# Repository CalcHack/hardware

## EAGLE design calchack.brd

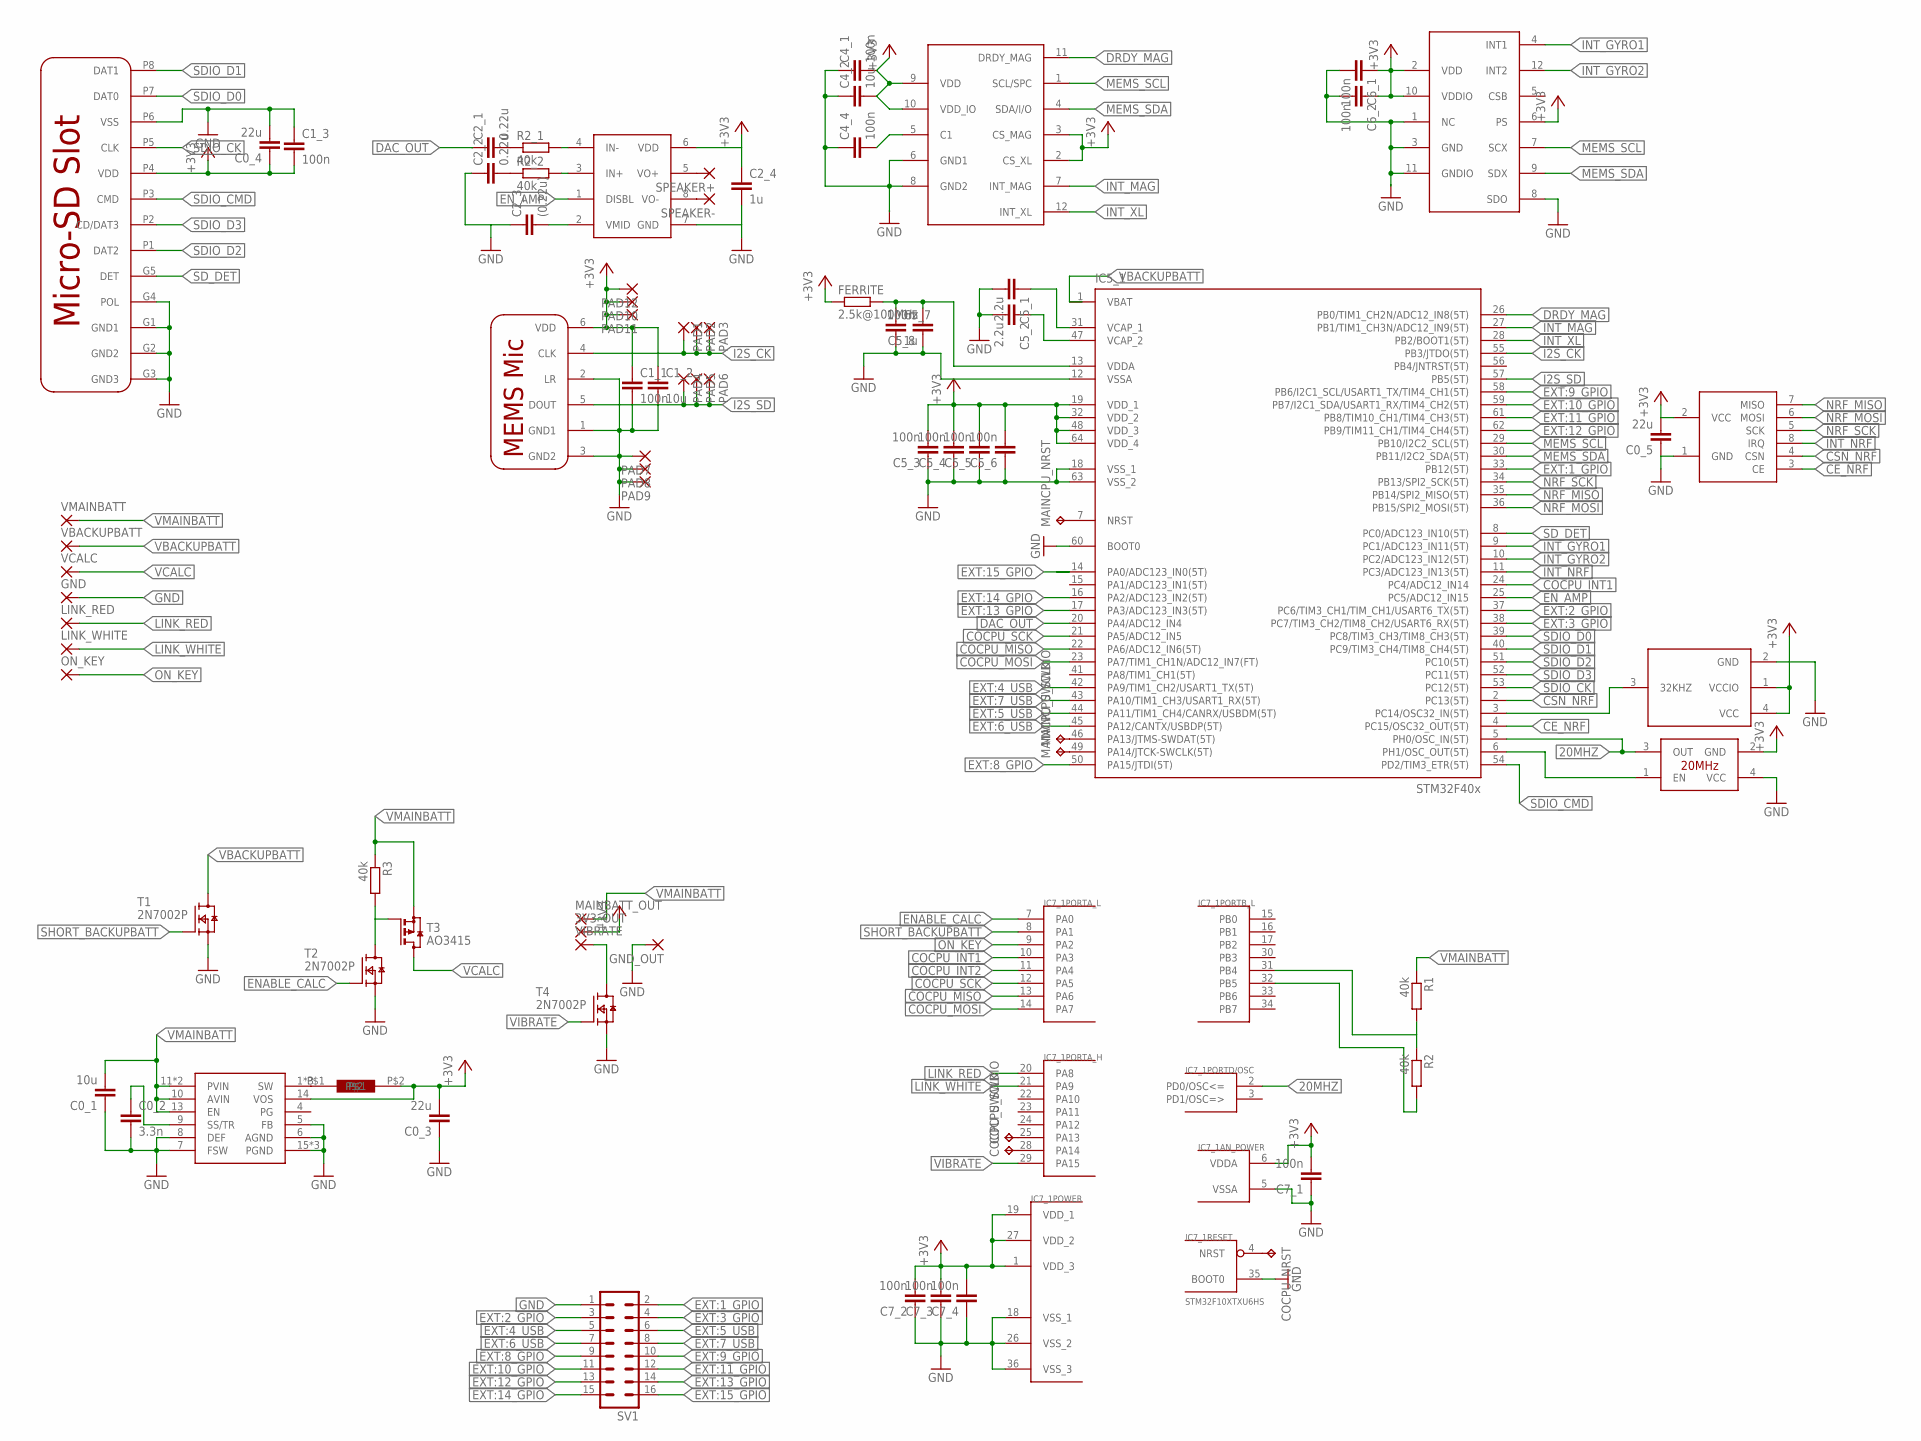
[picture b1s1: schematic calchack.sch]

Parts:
3V3_OUT: 1,6/0,8
C0_1: 10u; C0805
C0_2: 3.3n; C0603
C0_3, C0_4, C0_5: 22u; C0805
C1_1, C1_3, C4_1, C4_4, C5_3, C5_4, C5_5, C5_6, C5_8, C6_1, C6_2, C7_1, C7_2, C7_3, C7_4: 100n; C0603
C1_2, C4_2: 10u; C0603
C2_1, C2_2: 0.22u; C0603
C2_3: (0.22u); C0603
C2_4, C5_7: 1u; C0603
C5_1, C5_2: 2.2u; C0603
COCPU_NRST: TPTP10SQ; TP10SQ
COCPU_SWCLK: TPTP10SQ; TP10SQ
COCPU_SWDIO: TPTP10SQ; TP10SQ
FERRITE: 2.5k@100MHz; R0603
GND: 1,6/0,8
GND_OUT: 1,6/0,8
IC0_1: TPS62142
IC1_1: MP45DT02
IC2_1: TPA6211A1
IC3_1: 475710001
IC4_1: LSM303C
IC5_1: STM32F405R; TQFP64
IC6_1: BMG160
IC7_1: STM32F10XTXU6HS; VFQFPN36-HS
L0_1: IHLP1212BZER2R2M11
LINK_RED: 1,6/0,8
LINK_WHITE: 1,6/0,8
MAINBATT_OUT: 1,6/0,8
MAINCPU_NRST: TPTP10SQ; TP10SQ
MAINCPU_SWCLK: TPTP10SQ; TP10SQ
MAINCPU_SWDIO: TPTP10SQ; TP10SQ
NRF24L01: NRF24L01
ON_KEY: 1,6/0,8
OSC5_1: SG-3030JC
PAD1, PAD2, PAD3, PAD4, PAD5, PAD6, PAD7, PAD8, PAD9, PAD10, PAD11, PAD12: 1,6/0,8
R1, R2, R2_1, R2_2, R3: 40k; R0603
SPEAKER+: 1,6/0,8
SPEAKER-: 1,6/0,8
SV1: MA08-2
T1, T2, T4: 2N7002P; SOT23
T3: AO3415
U$1: ASDMB-20.000MHZ-LC-T
VBACKUPBATT: 1,6/0,8
VCALC: 1,6/0,8
VIBRATE: 1,6/0,8
VMAINBATT: 1,6/0,8

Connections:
20MHZ: IC5_1.5 (PH0/OSC_IN(5T)), IC7_1.2 (PD0/OSC<=), U$1.3 (OUT)
+3V3: 3V3_OUT.1, C0_3.2, C0_4.1, C0_5.2, C1_1.1, C1_2.1, C1_3.2, C2_4.1, C4_1.2, C4_2.2, C5_3.2, C5_4.2, C5_5.2, C5_6.2, C6_1.1, C6_2.1, C7_1.2, C7_2.2, C7_3.2, C7_4.2, FERRITE.1, IC0_1.14 (VOS), IC1_1.6 (VDD), IC2_1.6 (VDD), IC3_1.P4 (VDD), IC4_1.2 (CS_XL), IC4_1.3 (CS_MAG), IC4_1.9 (VDD), IC4_1.10 (VDD_IO), IC5_1.19 (VDD_1), IC5_1.32 (VDD_2), IC5_1.48 (VDD_3), IC5_1.64 (VDD_4), IC6_1.2 (VDD), IC6_1.6 (PS), IC6_1.10 (VDDIO), IC7_1.1 (VDD_3), IC7_1.6 (VDDA), IC7_1.19 (VDD_1), IC7_1.27 (VDD_2), L0_1.P$2, NRF24L01.2 (VCC), OSC5_1.1 (VCCIO), OSC5_1.4 (VCC), PAD10.1, PAD11.1, PAD12.1, U$1.2 (GND)
CE_NRF: IC5_1.4 (PC15/OSC32_OUT(5T)), NRF24L01.3 (CE)
COCPU_INT1: IC5_1.24 (PC4/ADC12_IN14), IC7_1.10 (PA3)
COCPU_INT2: IC7_1.11 (PA4)
COCPU_MISO: IC5_1.22 (PA6/ADC12_IN6(5T)), IC7_1.13 (PA6)
COCPU_MOSI: IC5_1.23 (PA7/TIM1_CH1N/ADC12_IN7(FT)), IC7_1.14 (PA7)
COCPU_SCK: IC5_1.21 (PA5/ADC12_IN5), IC7_1.12 (PA5)
CSN_NRF: IC5_1.2 (PC13(5T)), NRF24L01.4 (CSN)
DAC_OUT: C2_1.1, IC5_1.20 (PA4/ADC12_IN4)
DRDY_MAG: IC4_1.11 (DRDY_MAG), IC5_1.26 (PB0/TIM1_CH2N/ADC12_IN8(5T))
ENABLE_CALC: IC7_1.7 (PA0), T2.1 (G)
EN_AMP: IC2_1.1 (DISBL), IC5_1.25 (PC5/ADC12_IN15)
EXT:1_GPIO: IC5_1.33 (PB12(5T)), SV1.2
EXT:2_GPIO: IC5_1.37 (PC6/TIM3_CH1/TIM_CH1/USART6_TX(5T)), SV1.3
EXT:3_GPIO: IC5_1.38 (PC7/TIM3_CH2/TIM8_CH2/USART6_RX(5T)), SV1.4
EXT:4_USB: IC5_1.42 (PA9/TIM1_CH2/USART1_TX(5T)), SV1.5
EXT:5_USB: IC5_1.44 (PA11/TIM1_CH4/CANRX/USBDM(5T)), SV1.6
EXT:6_USB: IC5_1.45 (PA12/CANTX/USBDP(5T)), SV1.7
EXT:7_USB: IC5_1.43 (PA10/TIM1_CH3/USART1_RX(5T)), SV1.8
EXT:8_GPIO: IC5_1.50 (PA15/JTDI(5T)), SV1.9
EXT:9_GPIO: IC5_1.58 (PB6/I2C1_SCL/USART1_TX/TIM4_CH1(5T)), SV1.10
EXT:10_GPIO: IC5_1.59 (PB7/I2C1_SDA/USART1_RX/TIM4_CH2(5T)), SV1.11
EXT:11_GPIO: IC5_1.61 (PB8/TIM10_CH1/TIM4_CH3(5T)), SV1.12
EXT:12_GPIO: IC5_1.62 (PB9/TIM11_CH1/TIM4_CH4(5T)), SV1.13
EXT:13_GPIO: IC5_1.17 (PA3/ADC123_IN3(5T)), SV1.14
EXT:14_GPIO: IC5_1.16 (PA2/ADC123_IN2(5T)), SV1.15
EXT:15_GPIO: IC5_1.14 (PA0/ADC123_IN0(5T)), SV1.16
GND: C0_1.1, C0_2.2, C0_3.1, C0_4.2, C0_5.1, C1_1.2, C1_2.2, C1_3.1, C2_2.1, C2_3.1, C2_4.2, C4_1.1, C4_2.1, C4_4.1, C5_1.2, C5_2.2, C5_3.1, C5_4.1, C5_5.1, C5_6.1, C5_7.2, C5_8.1, C6_1.2, C6_2.2, C7_1.1, C7_2.1, C7_3.1, C7_4.1, GND.1, GND_OUT.1, IC0_1.5 (FB), IC0_1.6 (AGND), IC0_1.7 (FSW), IC0_1.8 (DEF), IC0_1.15 (PGND), IC0_1.16 (PGND), IC0_1.TH (PGND), IC1_1.1 (GND1), IC1_1.2 (LR), IC1_1.3 (GND2), IC2_1.7 (GND), IC3_1.G1 (GND1), IC3_1.G2 (GND2), IC3_1.G3 (GND3), IC3_1.G4 (POL), IC3_1.P6 (VSS), IC4_1.6 (GND1), IC4_1.8 (GND2), IC5_1.12 (VSSA), IC5_1.18 (VSS_1), IC5_1.60 (BOOT0), IC5_1.63 (VSS_2), IC6_1.1 (NC), IC6_1.3 (GND), IC6_1.8 (SDO), IC6_1.11 (GNDIO), IC7_1.5 (VSSA), IC7_1.18 (VSS_1), IC7_1.26 (VSS_2), IC7_1.35 (BOOT0), IC7_1.36 (VSS_3), NRF24L01.1 (GND), OSC5_1.2 (GND), PAD7.1, PAD8.1, PAD9.1, SV1.1, T1.2 (S), T2.2 (S), T4.2 (S), U$1.4 (VCC)
I2S_CK: IC1_1.4 (CLK), IC5_1.55 (PB3/JTDO(5T)), PAD1.1, PAD2.1, PAD3.1
I2S_SD: IC1_1.5 (DOUT), IC5_1.57 (PB5(5T)), PAD4.1, PAD5.1, PAD6.1
INT_GYRO1: IC5_1.9 (PC1/ADC123_IN11(5T)), IC6_1.4 (INT1)
INT_GYRO2: IC5_1.10 (PC2/ADC123_IN12(5T)), IC6_1.12 (INT2)
INT_MAG: IC4_1.7 (INT_MAG), IC5_1.27 (PB1/TIM1_CH3N/ADC12_IN9(5T))
INT_NRF: IC5_1.11 (PC3/ADC123_IN13(5T)), NRF24L01.8 (IRQ)
INT_XL: IC4_1.12 (INT_XL), IC5_1.28 (PB2/BOOT1(5T))
LINK_RED: IC7_1.20 (PA8), LINK_RED.1
LINK_WHITE: IC7_1.21 (PA9), LINK_WHITE.1
MEMS_SCL: IC4_1.1 (SCL/SPC), IC5_1.29 (PB10/I2C2_SCL(5T)), IC6_1.7 (SCX)
MEMS_SDA: IC4_1.4 (SDA/I/O), IC5_1.30 (PB11/I2C2_SDA(5T)), IC6_1.9 (SDX)
unnamed: IC2_1.3 (IN+), R2_2.2
unnamed: IC2_1.4 (IN-), R2_1.2
unnamed: C2_1.2, R2_1.1
unnamed: C2_2.2, R2_2.1
unnamed: C2_3.2, IC2_1.2 (VMID)
unnamed: IC5_1.6 (PH1/OSC_OUT(5T)), U$1.1 (EN)
unnamed: C4_4.2, IC4_1.5 (C1)
unnamed: C5_7.1, C5_8.2, FERRITE.2, IC5_1.13 (VDDA)
unnamed: COCPU_SWDIO.TP, IC7_1.25 (PA13)
unnamed: C0_2.1, IC0_1.9 (SS/TR)
unnamed: IC2_1.5 (VO+), SPEAKER+.1
unnamed: C5_2.1, IC5_1.47 (VCAP_2)
unnamed: C5_1.1, IC5_1.31 (VCAP_1)
unnamed: IC2_1.8 (VO-), SPEAKER-.1
unnamed: IC0_1.1 (SW), IC0_1.2 (SW), IC0_1.3 (SW), L0_1.P$1
unnamed: R3.2, T2.3 (D), T3.1 (G)
unnamed: COCPU_NRST.TP, IC7_1.4 (NRST)
unnamed: T4.3 (D), VIBRATE.1
unnamed: COCPU_SWCLK.TP, IC7_1.28 (PA14)
unnamed: IC5_1.49 (PA14/JTCK-SWCLK(5T)), MAINCPU_SWCLK.TP
unnamed: IC5_1.46 (PA13/JTMS-SWDAT(5T)), MAINCPU_SWDIO.TP
unnamed: IC5_1.3 (PC14/OSC32_IN(5T)), OSC5_1.3 (32KHZ)
unnamed: IC5_1.7 (NRST), MAINCPU_NRST.TP
unnamed: IC7_1.31 (PB4), R1.2, R2.1
unnamed: IC7_1.32 (PB5), R2.2
NRF_MISO: IC5_1.35 (PB14/SPI2_MISO(5T)), NRF24L01.7 (MISO)
NRF_MOSI: IC5_1.36 (PB15/SPI2_MOSI(5T)), NRF24L01.6 (MOSI)
NRF_SCK: IC5_1.34 (PB13/SPI2_SCK(5T)), NRF24L01.5 (SCK)
ON_KEY: IC7_1.9 (PA2), ON_KEY.1
SDIO_CK: IC3_1.P5 (CLK), IC5_1.53 (PC12(5T))
SDIO_CMD: IC3_1.P3 (CMD), IC5_1.54 (PD2/TIM3_ETR(5T))
SDIO_D0: IC3_1.P7 (DAT0), IC5_1.39 (PC8/TIM3_CH3/TIM8_CH3(5T))
SDIO_D1: IC3_1.P8 (DAT1), IC5_1.40 (PC9/TIM3_CH4/TIM8_CH4(5T))
SDIO_D2: IC3_1.P1 (DAT2), IC5_1.51 (PC10(5T))
SDIO_D3: IC3_1.P2 (CD/DAT3), IC5_1.52 (PC11(5T))
SD_DET: IC3_1.G5 (DET), IC5_1.8 (PC0/ADC123_IN10(5T))
SHORT_BACKUPBATT: IC7_1.8 (PA1), T1.1 (G)
VBACKUPBATT: IC5_1.1 (VBAT), T1.3 (D), VBACKUPBATT.1
VCALC: T3.3 (D), VCALC.1
VIBRATE: IC7_1.29 (PA15), T4.1 (G)
VMAINBATT: C0_1.2, IC0_1.10 (AVIN), IC0_1.11 (PVIN), IC0_1.12 (PVIN), IC0_1.13 (EN), MAINBATT_OUT.1, R1.1, R3.1, T3.2 (S), VMAINBATT.1

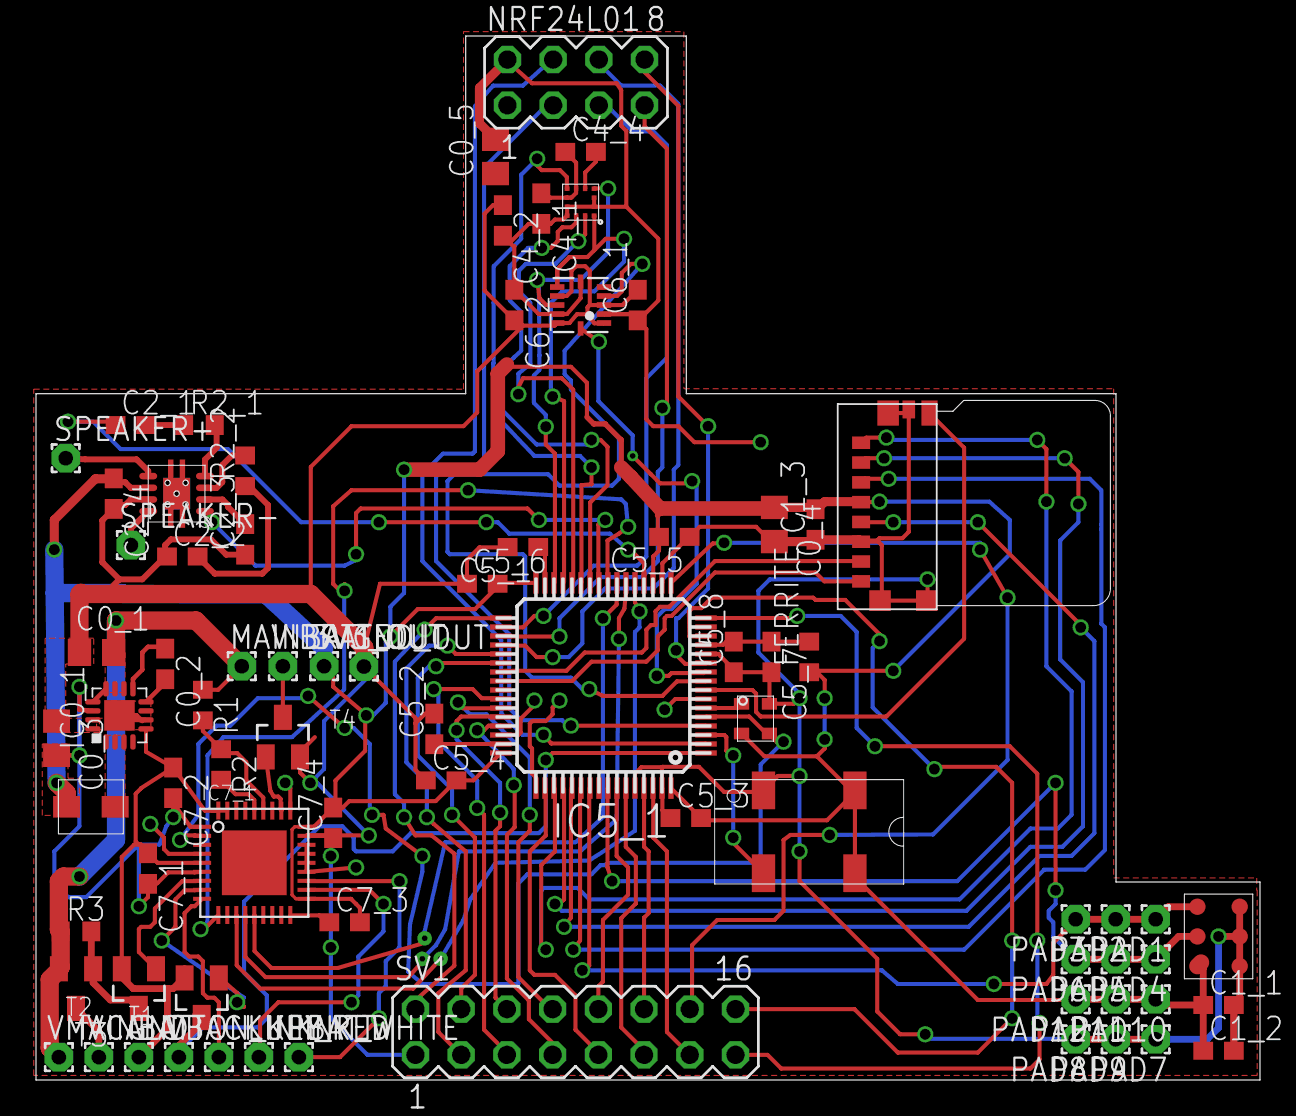
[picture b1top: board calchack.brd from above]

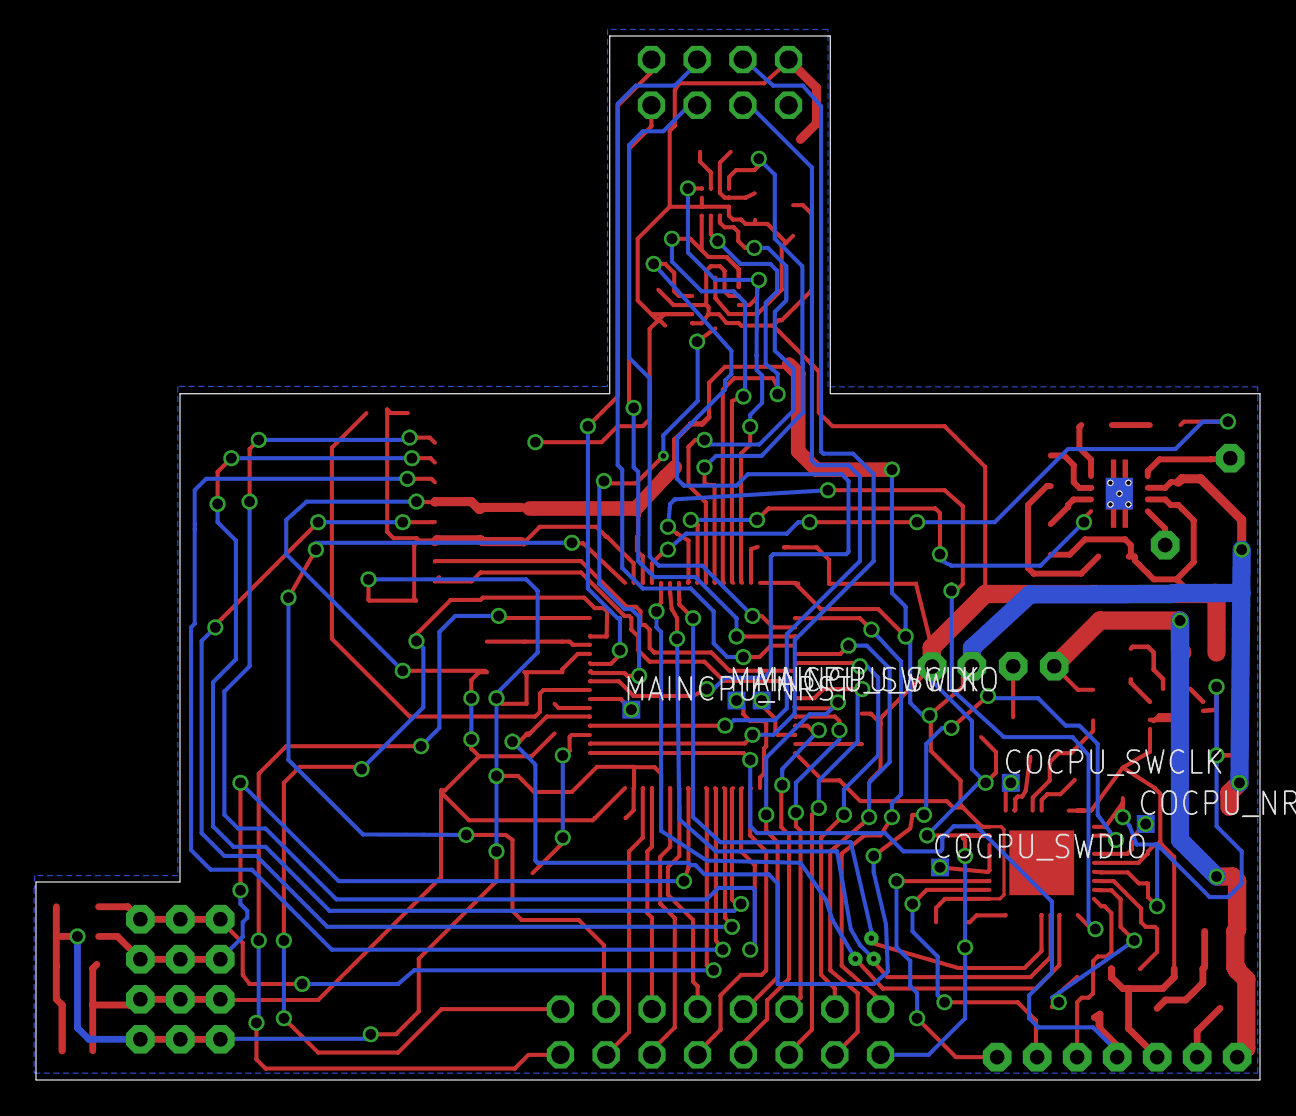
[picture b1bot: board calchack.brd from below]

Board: 2 copper layers, 68.0 x 58.0 mm, 83 parts (6 on the bottom side), 80 nets.
